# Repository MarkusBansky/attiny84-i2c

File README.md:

# attiny84-i2c
An open-source pcb design for a compact programmable I2C circuit based on Attiny84 microcontroller
This board was developed for educational purpose. It is open-source and free to make for yourself with all project files available on GitHub.

In the heart of this board is the ATtiny84 - a cheap and easy to use microcontroller. This microcontroller can run at a very low power consumption rate, ranging just 0.1 - 300 μA at only 1.8V and 1 MHz clock speed.

The basic configuration advised for this board is the following:

- Li-Ion battery power source (note, that this board does not include battery charger circuit)
- 1 MHz internal clock speed
- Counterclockwise pinout
- No bootloader
- Use Arduino IDE

This board can be programmed via Arduino IDE. For this purpose there are Programmer pins exposed in the top left corner of the board. They can be inserted temporarily for programming only or soldered for more frequent use. 

Controller uses only internal clocks, and I personally would advise you to use the 1 MHz internal clock, it is the most medium efficient option between the power consumption and speed.

This board has a battery connector called BAT2, it has two pins and is used for single cell Li-Ion batteries. Please kindly note that this board is not able to charge the battery as it does not contain the charging circuit. This option is noted for the next version of the board.

Each of Analog pinouts contains a ground and power pins as well as a single analog input pin that can be connected either to ground or to +3.3V on purpose but soldering the jumpers on the bottom side of the board.

Two Qwiic connectors are available in the bottom part of the board, granting you access to either two peripherals via I2C interface or a input-output mode, to make this board able to operate as master and as a slave.

The Reset button let’s you reset the microcontroller on purpose, and a green Status LED on top of it indicates the power going through the circuit.

User has an opportunity to program a built-in LED connected to port 6. Please check the IDE pinout before.

To program this board I would advise you to use the ATtinyCore available through arduino IDE. You should have any USB Arduino board to use as Arduino ISP.

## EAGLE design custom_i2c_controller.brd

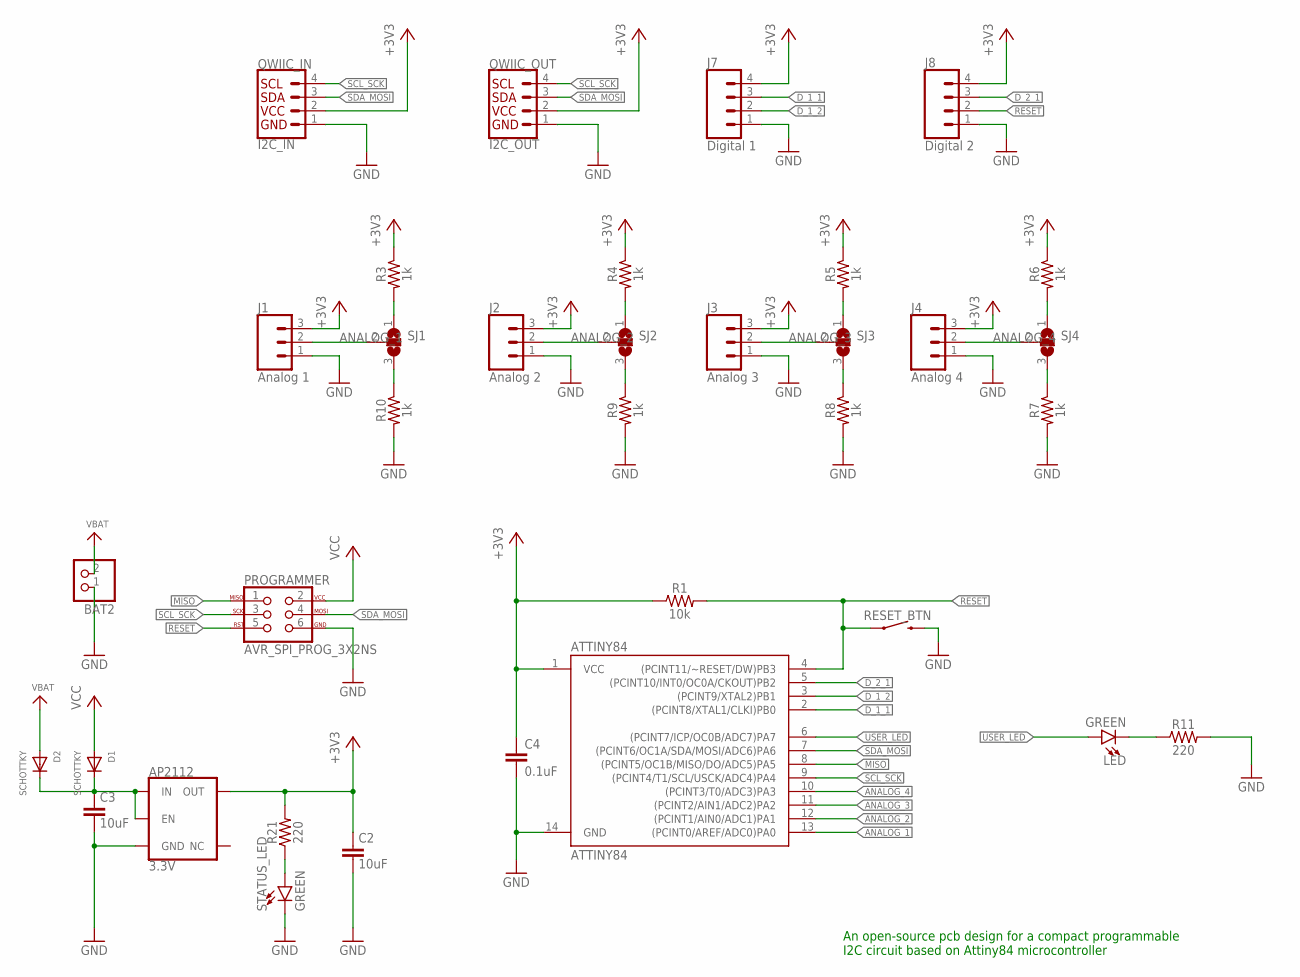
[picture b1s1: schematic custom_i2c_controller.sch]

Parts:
AP2112: 3.3V; SOT23-5
ATTINY84: ATTINY84; SO14
BAT2: CON_JST_PH_2PINSH2; JSTSH2
C2, C3: 10uF; 1206
C4: 0.1uF; 0603
D1, D2: SCHOTTKY; SOD-123FL
J1: Analog 1; 1X03
J2: Analog 2; 1X03
J3: Analog 3; 1X03
J4: Analog 4; 1X03
J7: Digital 1; 1X04
J8: Digital 2; 1X04
LED: GREEN; LED-0603
PROGRAMMER: AVR_SPI_PROG_3X2NS; 2X3-NS
QWIIC_IN: I2C_IN; 1X04_1MM_RA
QWIIC_OUT: I2C_OUT; 1X04_1MM_RA
R1: 10k; 0603
R3, R4, R5, R6, R7, R8, R9, R10: 1k; 0603
R11, R21: 220; 0603
RESET_BTN: MOMENTARY-SWITCH-SPST-SMD-6.0X3.5MM; TACTILE_SWITCH_SMD_6.0X3.5MM
SJ1, SJ2, SJ3, SJ4: SJ2W; SJ_2
STATUS_LED: GREEN; LED-0603

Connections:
+3V3: AP2112.5 (OUT), ATTINY84.1 (VCC), C2.1, C4.1, J1.3, J2.3, J3.3, J4.3, J7.4, J8.4, QWIIC_IN.2 (VCC), QWIIC_OUT.2 (VCC), R1.1, R3.1, R4.1, R5.1, R6.1, R21.2
ANALOG_1: ATTINY84.13 ((PCINT0/AREF/ADC0)PA0), J1.2, SJ1.2
ANALOG_2: ATTINY84.12 ((PCINT1/AIN0/ADC1)PA1), J2.2, SJ2.2
ANALOG_3: ATTINY84.11 ((PCINT2/AIN1/ADC2)PA2), J3.2, SJ3.2
ANALOG_4: ATTINY84.10 ((PCINT3/T0/ADC3)PA3), J4.2, SJ4.2
D_1_1: ATTINY84.2 ((PCINT8/XTAL1/CLKI)PB0), J7.3
D_1_2: ATTINY84.3 ((PCINT9/XTAL2)PB1), J7.2
D_2_1: ATTINY84.5 ((PCINT10/INT0/OC0A/CKOUT)PB2), J8.3
GND: AP2112.2 (GND), ATTINY84.14 (GND), BAT2.1, C2.2, C3.2, C4.2, J1.1, J2.1, J3.1, J4.1, J7.1, J8.1, PROGRAMMER.6, QWIIC_IN.1 (GND), QWIIC_OUT.1 (GND), R7.2, R8.2, R9.2, R10.2, R11.2, RESET_BTN.2, STATUS_LED.C
MISO: ATTINY84.8 ((PCINT5/OC1B/MISO/DO/ADC5)PA5), PROGRAMMER.1
unnamed: R7.1, SJ4.3
unnamed: R6.2, SJ4.1
unnamed: R8.1, SJ3.3
unnamed: R5.2, SJ3.1
unnamed: R4.2, SJ2.1
unnamed: R9.1, SJ2.3
unnamed: R10.1, SJ1.3
unnamed: R3.2, SJ1.1
unnamed: R21.1, STATUS_LED.A
unnamed: AP2112.1 (IN), AP2112.3 (EN), C3.1, D1.C, D2.C
unnamed: LED.C, R11.1
RESET: ATTINY84.4 ((PCINT11/~RESET/DW)PB3), J8.2, PROGRAMMER.5, R1.2, RESET_BTN.1
SCL_SCK: ATTINY84.9 ((PCINT4/T1/SCL/USCK/ADC4)PA4), PROGRAMMER.3, QWIIC_IN.4 (SCL), QWIIC_OUT.4 (SCL)
SDA_MOSI: ATTINY84.7 ((PCINT6/OC1A/SDA/MOSI/ADC6)PA6), PROGRAMMER.4, QWIIC_IN.3 (SDA), QWIIC_OUT.3 (SDA)
USER_LED: ATTINY84.6 ((PCINT7/ICP/OC0B/ADC7)PA7), LED.A
VBAT: BAT2.2, D2.A
VCC: D1.A, PROGRAMMER.2

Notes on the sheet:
An open-source pcb design for a compact programmable I2C circuit based on Attiny84 microcontroller

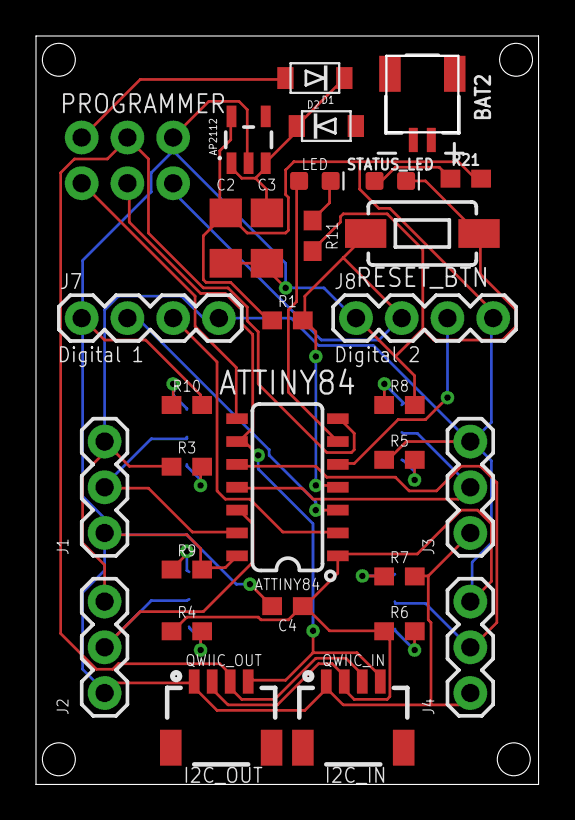
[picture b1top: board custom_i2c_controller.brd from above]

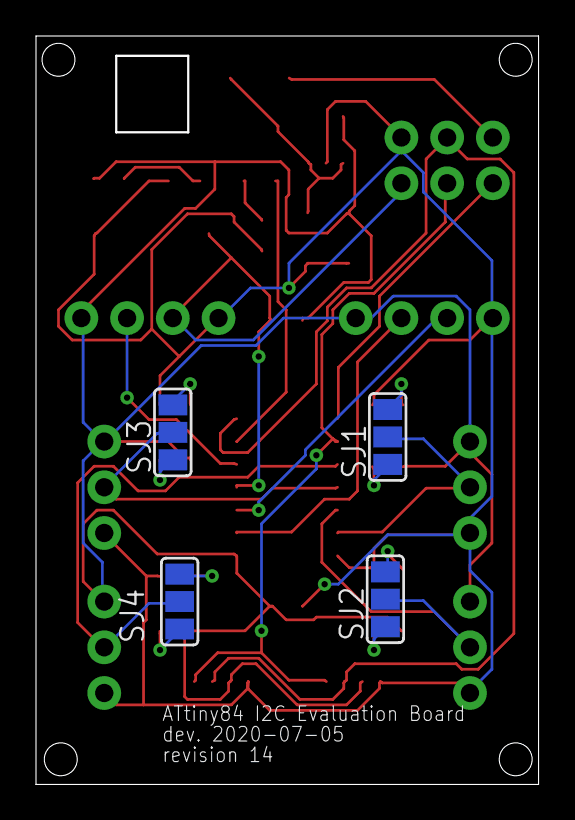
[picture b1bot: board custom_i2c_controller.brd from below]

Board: 2 copper layers, 27.8 x 41.5 mm, 35 parts (4 on the bottom side), 27 nets.

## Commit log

2020-07-07 Added project files
    Adding EAGLE project files to this repository.
    - the **.brd** file contains information about the board design.
    - the **.sch** file contains the schematic design of the board circuit.
    - the **eagle.epf** is the main project file for EAGLE application.

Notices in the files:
parts and their libraries:
SparkFun-IC-Power: Licensing: Creative Commons ShareAlike 4.0 International - https://creativecommons.org/licenses/by-sa/4.0
microbuilder: This work is placed in the public domain, and may be freely used for commercial and non-commercial work with the following conditions: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
